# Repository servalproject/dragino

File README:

This is the build tree for OpenWRT on the Dragino, including
the Serval Daemon (servald aka serval-dna), and appropriate
default configuration for running the dragino as a mesh
helper device.

See http://developer.servalproject.org/dokuwiki/doku.php?id=content:meshhelper:main_page
for further explanation.

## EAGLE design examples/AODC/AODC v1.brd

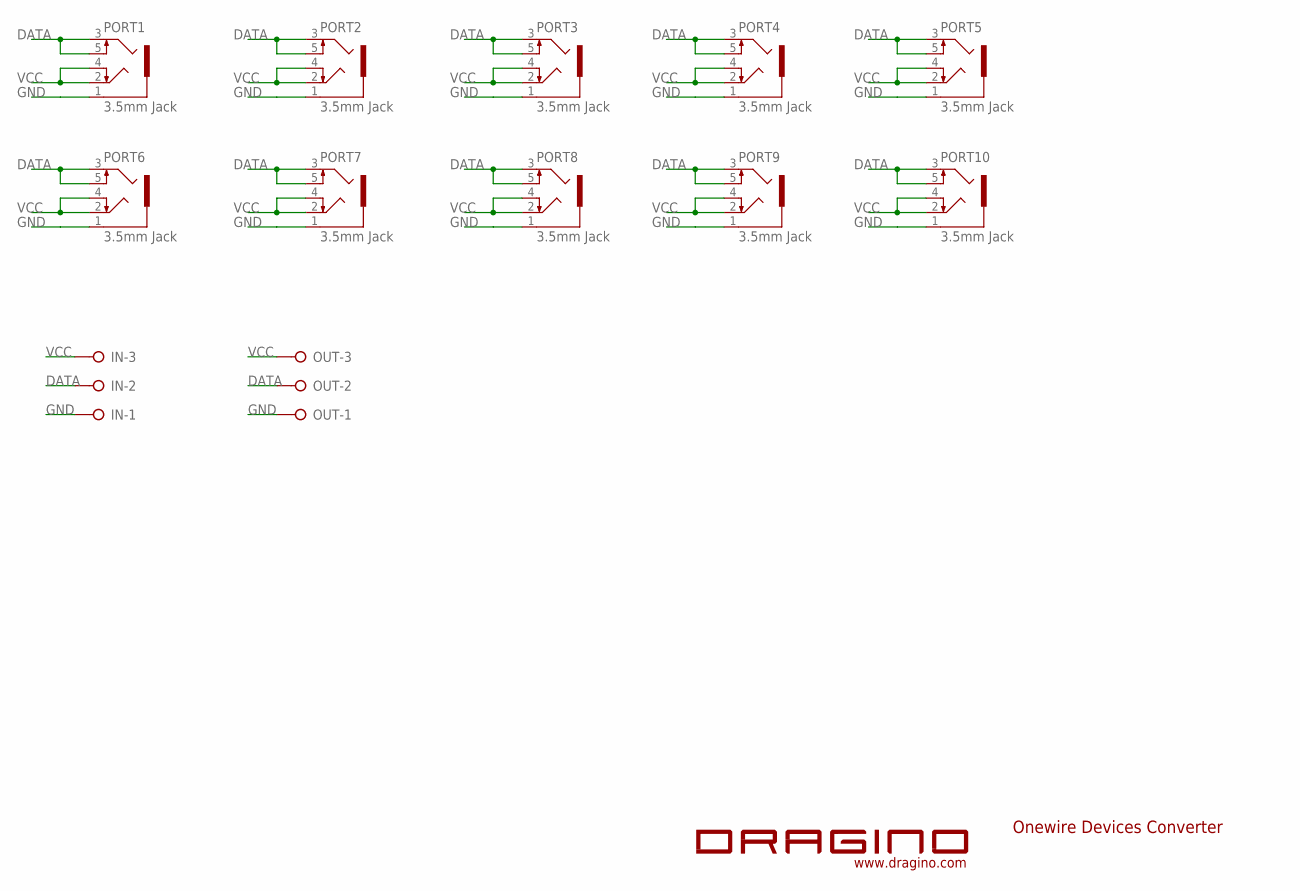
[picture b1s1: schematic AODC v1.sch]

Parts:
IN: SCREW-TERMINAL-3P; W237-3E
OUT: SCREW-TERMINAL-3P; W237-3E
PORT1, PORT2, PORT3, PORT4, PORT5, PORT6, PORT7, PORT8, PORT9, PORT10: 3.5mm Jack; AUDIO-JACK-3.5MM
U$1: LOGO-SILK; LOGO-SILK-15MM

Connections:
DATA: IN.2, OUT.2, PORT1.3, PORT1.5, PORT2.3, PORT2.5, PORT3.3, PORT3.5, PORT4.3, PORT4.5, PORT5.3, PORT5.5, PORT6.3, PORT6.5, PORT7.3, PORT7.5, PORT8.3, PORT8.5, PORT9.3, PORT9.5, PORT10.3, PORT10.5
GND: IN.1, OUT.1, PORT1.1, PORT2.1, PORT3.1, PORT4.1, PORT5.1, PORT6.1, PORT7.1, PORT8.1, PORT9.1, PORT10.1
VCC: IN.3, OUT.3, PORT1.2, PORT1.4, PORT2.2, PORT2.4, PORT3.2, PORT3.4, PORT4.2, PORT4.4, PORT5.2, PORT5.4, PORT6.2, PORT6.4, PORT7.2, PORT7.4, PORT8.2, PORT8.4, PORT9.2, PORT9.4, PORT10.2, PORT10.4

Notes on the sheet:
Onewire Devices Converter

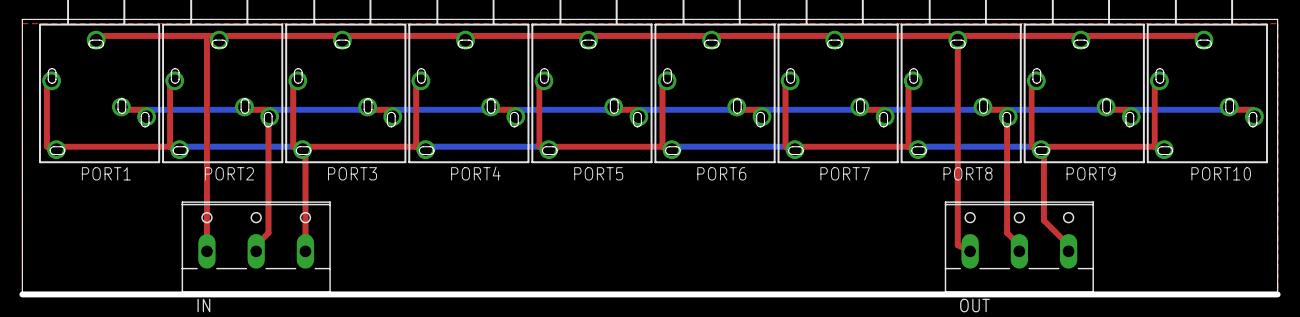
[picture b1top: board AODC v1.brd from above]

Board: 2 copper layers, 129.5 x 28.1 mm, 13 parts (0 on the bottom side), 3 nets.

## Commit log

2011-11-09 Examples to show how to work with avr MCU
2011-11-30 Add OpenWrt Directory
2011-12-21 add script for auto upgrade avr image.
2011-12-21 update Serial to Pachube demo code
2011-12-23 add SPI test example with avr.
2011-12-23 remove old spi_incoming code
2012-01-10 Add exception of empty hex file
2012-02-08 1)Change sensor dataformat to match the new Dragino firmware. 2)Add hex file
2012-02-08 SPI demo code to show how to send data from Dragrove and get feedback
2012-02-10 Fix Header Error
2012-03-09 Orignal build of this OpenWRT firmware is from Flukso(www.flukso.net) and adapted to suit the Dragino project.
2012-04-12 1) add Upgrade page, now user can upload Dragino firmware via GUI. 2) add timezone option, can change timezone now via system page.
2012-04-27 remove flukso.service from Avahi
2012-05-11 remove restful service
2012-05-11 1) update version number 2) change Web CSS style 3) modify network setting to make it easier to switch between wifi and Rj45.
2012-05-19 add upgrade page logo
2012-05-19 1) Update Pachube to Cosm 2) comment local var to build luci in Ubuntu 12.04
2012-05-22 Add firmware check into first boot
2012-05-28 opps!
2012-05-28 upgrade firmware page in WEB
2012-06-05 add Chinese Support in Luci
2012-06-05 add Chinese support
2012-06-06 1)add language option in GUI 2)update firmware version number to 2.1
2012-06-16 add IoT service provider
2012-06-16 1) add support for general IoT server. detail of how to use please refer wiki.dragino.com
2012-09-28 add transparent mode. in transparent mode, we won't do data validity on the date comes from UART port.
2012-09-28 add flag for transparent mode
2012-09-29 add source code for MT-DS
2012-10-01 Add Eagle files for 1-Wire Devices Converter.
2012-10-29 add hex file
2012-11-26 imported serval-dna openwrt makefile from github.com/servalproject/servaldna/openwrt/packages/serval-dna/Makefile
2012-11-26 change default wifi configuration to ahdemo + 2x access points.
2012-11-26 added basic README.
2012-11-26 added link to serval project wiki explaining why this repository exists.
2012-11-26 build serval-dna as part of firmware by default.
2012-11-27 added default IP configuration for public and private virtual access points.
2012-11-27 added /etc/init.d/setmeship to set a random IP in 28.0.0.0/7 for the mesh interface following the Serval Mesh standard. Set to run at boot just before bringing up the network.
2012-11-27 moved setmeship script and fixed two bugs.
2012-11-27 added OSX binary for ap51-flash, and instructions on where to get the source for ap51-flash, since it is GPL software.
2012-11-28 enable DHCP leases on VAPs
2012-11-28 added dns masquerading to point any web request to local web server that will eventually host HTML client for Serval services.
2012-11-28 start servald on boot, and rename S39setmeship to more informative and general S39servalmesh. Also add stop() function to this that will stop servald.
2012-11-28 stop ignoring ARP requests (grrr)
2012-11-28 pull in latest serval-dna to hopefully stop segfault on startup due to network interfaces not yet being up.
2012-11-28 added scripts for flashing Dragino from a mac, since mac version of ap51-flash seems to botch the job.
2012-11-28 split servald config and startup to avoid problems with servald starting before network interfaces come up.
2012-11-28 fixed broken line.
2012-12-04 don't block broadcast pings (at least while we are developing the base distribution).
2012-12-04 make servald instance path default to /etc/serval
2012-12-04 remove environment variable setting now that servald can be made to have its instance path in the right place at compile time.
2012-12-21 put rhizome database in tmpfs instead of on flash, as flash is INSANELY slow on the Dragino. limit rhizome RX buffer sizes to reduce memory usage.
2012-12-21 use latest serval-dna that supports required features.

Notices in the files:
parts and their libraries:
frames: http://creativecommons.org/licenses/by-sa/3.0
frames: Released under the CC Attribution Share-Alike 3.0 License
